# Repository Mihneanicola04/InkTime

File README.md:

# InkTime - Smartwatch Open Source

**InkTime** este un start-up dedicat crearii unui smartwatch accesibil si open-source. Acest repository contine documentatia tehnica, fisierele de proiectare hardware (schematica si layout PCB), fisierele de productie si modelele 3D necesare pentru fabricarea dispozitivului.

## 1. Diagrama Bloc
Diagrama de mai jos ilustreaza arhitectura sistemului, evidentiind interconexiunile dintre microcontrolerul nRF52840 si modulele periferice (Display, IMU, Alimentare).

---

## 2. Bill of Materials (BOM)
Toate componentele au fost selectate pentru a fi compatibile cu asamblarea automata prin JLC PCB.

| Componenta / Modul | Descriere | Link Achizitie (JLC Parts) | Datasheet |
| :--- | :--- | :--- | :--- |
| **nRF52840** | SoC Bluetooth Low Energy | [Link JLC](https://jlcpcb.com/parts) | (https://infocenter.nordicsemi.com/) |
| **Display E-Paper** | Ecran cu consum redus | [Link JLC](https://jlcpcb.com/parts) |(https://jlcpcb.com/parts) |
| **Baterie Li-Po** | 3.7V, conectare directa pe pad-uri | [Link JLC](https://jlcpcb.com/parts) |(https://jlcpcb.com/parts) |
| **Senzor IMU** | Senzor de miscare (Accel/Gyro) | [Link JLC](https://jlcpcb.com/parts) | (https://jlcpcb.com/parts) |
| **Butoane SMD** | Tip 0201/0402 conform cerintelor | [Link JLC](https://jlcpcb.com/parts) |(https://jlcpcb.com/parts) |
| **Condensatoare** | 100nF (0201) / >100nF (0402) | [Link JLC](https://jlcpcb.com/parts) |(https://jlcpcb.com/parts) |

---

## 3. Functionalitate Hardware si Design

### Detalii Tehnice
* **Unitate de procesare:** nRF52840, ales pentru integrarea BLE si eficienta energetica.
* **Interfete de comunicatie:**
    * **SPI:** Utilizat pentru controlul ecranului e-paper pentru rate de refresh optime.
    * **I2C:** Utilizat pentru senzorul IMU si managementul bateriei.
* **Managementul energiei:** PCB-ul include circuite de protectie pentru bateria Li-Po. Consumul a fost optimizat prin utilizarea condensatoarelor de decuplare de 100nF amplasate imediat langa pinii de alimentare. Autonomia a fost calculata avand in vedere starea de sleep si timpii activi ai procesorului si display-ului.
* **PCB Design:** * Grosime PCB: **1mm**.
    * Trasee de putere (VCC, 3V3): **0.3mm**.
    * Trasee de date: **0.15mm**.
    * Plan de masa: Prezent pe ambele straturi (Top/Bottom) cu **Via Stitching** pentru integritatea semnalului radio.

### Mapare Pini nRF52840
| Pin nRF52840 | Componenta | Functie / Justificare |
| :--- | :--- | :--- |
| **P0.xx** | SPI CLK | Clock pentru ecranul e-paper |
| **P0.yy** | I2C SDA | Date pentru senzorul IMU |
| **P0.zz** | Buton 1 | Intrare digitala cu pull-up intern |
| **VBUS** | USB-C | Detectare alimentare si incarcare baterie |

---

## 4. Implementare si Decizii de Proiectare (Design Log)

In cadrul procesului de dezvoltare (EVT/DVT), s-au luat urmatoarele decizii tehnice:
1.  **Amplasare Componente:** Toate componentele au fost plasate pe layer-ul **TOP** pentru a simplifica procesul de fabricatie.
2.  **Antena:** A fost plasata la extremitatea placii, cu planul de masa decupat dedesubt pentru a evita atenuarea semnalului BLE.
3.  **Conectivitate Baterie:** Din ratiuni de spatiu in carcasa, s-a renuntat la conectorul JST, bateria fiind lipita direct pe test pad-urile dedicate.
4.  **Erori Acceptate:** Eroarea DRC "Only INPUT pins on NET ID" a fost ignorata conform specificatiilor, fiind un artefact al bibliotecii de simboluri.
5.  **Mecanica:** Carcasa a fost ajustata in Fusion360 pentru a asigura alinierea perfecta a portului USB-C si a butoanelor fizice.
---

## 5. Structura Repository
* `/Hardware`: Fisiere native Fusion360 (.sch, .brd).
* `/Manufacturing`: Fisiere Gerber, BOM si Pick and Place.
* `/Mechanical`: Modele 3D (STEP/Exploded view) si asamblarea in Fusion360.
* `/Images`: Randari ale produsului finit si ale PCB-ului.
---

## 6   . Licenta
Acest proiect este licentiat sub [Apache License 2.0](LICENSE).

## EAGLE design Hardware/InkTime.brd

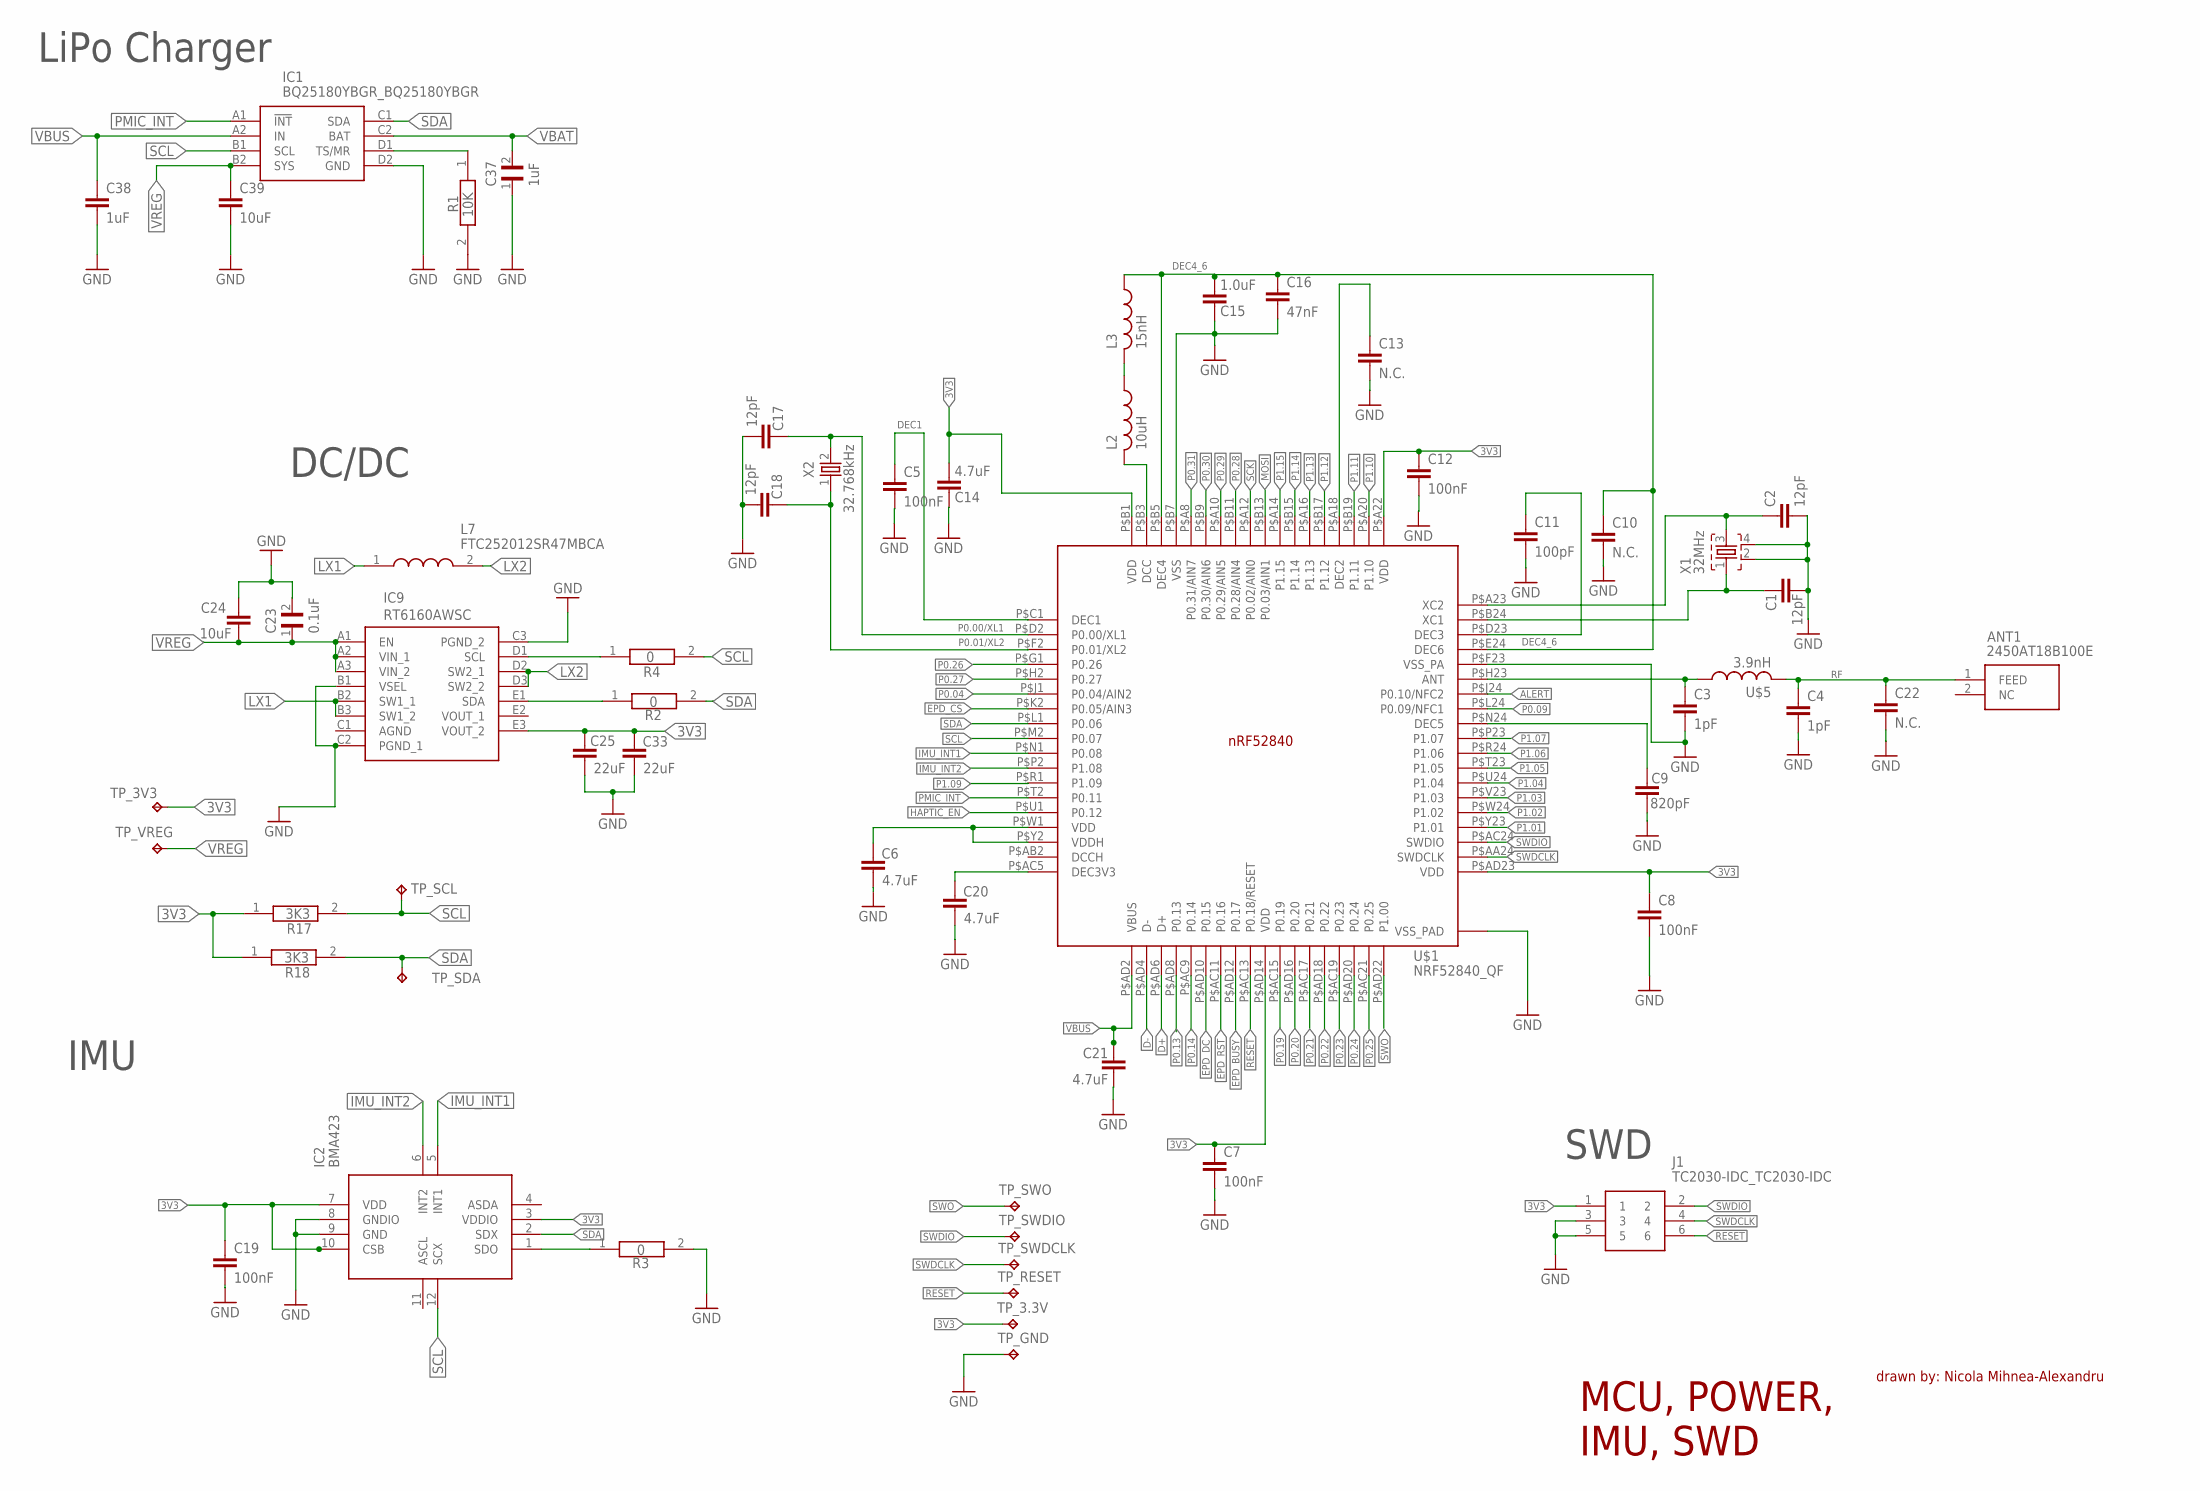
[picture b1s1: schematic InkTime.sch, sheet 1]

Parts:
ANT1: 2450AT18B100E; 2450AT18B100E_ANTC3216X140N
C1, C2, C17, C18: 12pF; NORDIC_NRF_3_RESC0201_N
C3, C4: 1pF; NORDIC_NRF_3_RESC0201_N
C5, C7, C8, C12, C19: 100nF; NORDIC_NRF_3_RESC0201_N
C6, C14, C20, C21: 4.7uF; NORDIC_NRF_3_RESC0402_N
C9: 820pF; NORDIC_NRF_3_RESC0201_N
C10, C13, C22: N.C.; NORDIC_NRF_3_RESC0201_N
C11: 100pF; NORDIC_NRF_3_RESC0201_N
C15: 1.0uF; NORDIC_NRF_3_RESC0402_N
C16: 47nF; NORDIC_NRF_3_RESC0201_N
C23: 0.1uF; GRM011R60J152KE01L_2_CAPC0201X13N
C24, C39: 10uF; NORDIC_NRF_3_RESC0402_N
C25, C33: 22uF; NORDIC_NRF_3_RESC0402_N
C37: 1uF; GRM011R60J152KE01L_2_CAPC0201X13N
C38: 1uF; NORDIC_NRF_3_RESC0402_N
IC1: BQ25180YBGR_BQ25180YBGR; BQ25180YBGR_BGA8C40P2X4_100X155X50
IC2: BMA423; BMA423_BMA423
IC9: RT6160AWSC; RT6160AWSC_BGA15C40P3X5_140X230X60
J1: TC2030-IDC_TC2030-IDC; TC2030-IDC_TC2030IDC
L2: 10uH; NORDIC_NRF_2_RESC0201_N
L3: 15nH; NORDIC_NRF_2_RESC0201_N
L7: FTC252012SR47MBCA; MLP2016SR47MT0S1_INDC2016X100N
R1: 10K; CPF0201D7K68C1_0201
R2, R3, R4: 0; CPF0201D7K68C1_0201
R17, R18: 3K3; CPF0201D7K68C1_0201
TP_3.3V, TP_3V3: HECTOR_WATCH_1_TPTP20R; HECTOR_WATCH_1_TP20R
TP_GND: HECTOR_WATCH_1_TPTP20R; HECTOR_WATCH_1_TP20R
TP_RESET: HECTOR_WATCH_1_TPTP20R; HECTOR_WATCH_1_TP20R
TP_SCL: HECTOR_WATCH_1_TPTP20R; HECTOR_WATCH_1_TP20R
TP_SDA: HECTOR_WATCH_1_TPTP20R; HECTOR_WATCH_1_TP20R
TP_SWDCLK: HECTOR_WATCH_1_TPTP20R; HECTOR_WATCH_1_TP20R
TP_SWDIO: HECTOR_WATCH_1_TPTP20R; HECTOR_WATCH_1_TP20R
TP_SWO: HECTOR_WATCH_1_TPTP20R; HECTOR_WATCH_1_TP20R
TP_VREG: HECTOR_WATCH_1_TPTP20R; HECTOR_WATCH_1_TP20R
U$1: NRF52840_QF; NORDIC_NRF_4_AQFN50P700X700X85_HS-74N
U$5: 3.9nH; NORDIC_NRF_2_RESC0201_N
X1: 32MHz; NORDIC_NRF_BT-XTAL_2016_N
X2: 32.768kHz; NORDIC_NRF_1_XTAL_3215_N

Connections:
3V3: C7.1, C8.1, C12.1, C14.2, C19.1, C25.1, C33.1, IC2.3 (VDDIO), IC9.E3 (VOUT_2), J1.1, R17.1, R18.1, TP_3.3V.TP, TP_3V3.TP, U$1.P$A22 (VDD), U$1.P$AD14 (VDD), U$1.P$AD23 (VDD), U$1.P$B1 (VDD); also elsewhere on the board
ALERT: U$1.P$J24 (P0.10/NFC2); also elsewhere on the board
D+: U$1.P$AD6 (D+); also elsewhere on the board
D-: U$1.P$AD4 (D-); also elsewhere on the board
DEC1: C5.1, U$1.P$C1 (DEC1)
DEC4_6: C10.1, C15.2, C16.1, L3.1, U$1.P$B5 (DEC4), U$1.P$E24 (DEC6)
EPD_BUSY: U$1.P$AD12 (P0.17); also elsewhere on the board
EPD_CS: U$1.P$K2 (P0.05/AIN3); also elsewhere on the board
EPD_DC: U$1.P$AD10 (P0.15); also elsewhere on the board
EPD_RST: U$1.P$AC11 (P0.16); also elsewhere on the board
GND: C1.2, C2.2, C3.2, C4.2, C5.2, C6.2, C7.2, C8.2, C9.2, C10.2, C11.2, C12.2, C13.2, C14.1, C15.1, C16.2, C17.2, C18.2, C19.2, C20.2, C21.2, C22.2, C23.2, C24.1, C25.2, C33.2, C37.1, C38.2, C39.2, IC1.D2 (GND), IC2.8 (GNDIO), IC2.9 (GND), IC9.B1 (VSEL), IC9.C2 (PGND_1), IC9.C3 (PGND_2), J1.3, J1.5, R1.2, R3.2, TP_GND.TP, U$1.P$74 (VSS_PAD), U$1.P$75 (VSS_PAD), U$1.P$76 (VSS_PAD), U$1.P$77 (VSS_PAD), U$1.P$78 (VSS_PAD), U$1.P$79 (VSS_PAD), U$1.P$80 (VSS_PAD), U$1.P$81 (VSS_PAD), U$1.P$82 (VSS_PAD), U$1.P$83 (VSS_PAD), U$1.P$84 (VSS_PAD), U$1.P$85 (VSS_PAD), U$1.P$86 (VSS_PAD), U$1.P$87 (VSS_PAD), U$1.P$88 (VSS_PAD), U$1.P$89 (VSS_PAD), U$1.P$90 (VSS_PAD), U$1.P$B7 (VSS), U$1.P$F23 (VSS_PA), X1.2, X1.4; also elsewhere on the board
HAPTIC_EN: U$1.P$U1 (P0.12); also elsewhere on the board
IMU_INT1: IC2.5 (INT1), U$1.P$N1 (P0.08)
IMU_INT2: IC2.6 (INT2), U$1.P$P2 (P1.08)
LX1: IC9.B2 (SW1_1), IC9.B3 (SW1_2), L7.1
LX2: IC9.D2 (SW2_1), IC9.D3 (SW2_2), L7.2
MOSI: U$1.P$B13 (P0.03/AIN1); also elsewhere on the board
unnamed: C20.1, U$1.P$AC5 (DEC3V3)
unnamed: IC9.D1 (SCL), R4.1
unnamed: IC9.E1 (SDA), R2.1
unnamed: IC1.D1 (TS/MR), R1.1
unnamed: C6.1, U$1.P$W1 (VDD)
unnamed: IC2.7 (VDD), IC2.10 (CSB)
unnamed: L2.2, U$1.P$B3 (DCC)
unnamed: L2.1, L3.2
unnamed: IC2.1 (SDO), R3.1
unnamed: C11.1, U$1.P$D23 (DEC3)
unnamed: C2.1, U$1.P$A23 (XC2), X1.3
unnamed: C13.1, U$1.P$A18 (DEC2)
unnamed: C1.1, U$1.P$B24 (XC1), X1.1
unnamed: C3.1, U$1.P$H23 (ANT), U$5.1
unnamed: C9.1, U$1.P$N24 (DEC5)
P0.00/XL1: C17.1, U$1.P$D2 (P0.00/XL1), X2.2
P0.01/XL2: C18.1, U$1.P$F2 (P0.01/XL2), X2.1
P0.04: U$1.P$J1 (P0.04/AIN2)
P0.09: U$1.P$L24 (P0.09/NFC1)
P0.13: U$1.P$AD8 (P0.13); also elsewhere on the board
P0.14: U$1.P$AC9 (P0.14); also elsewhere on the board
P0.19: U$1.P$AC15 (P0.19)
P0.20: U$1.P$AD16 (P0.20)
P0.21: U$1.P$AC17 (P0.21)
P0.22: U$1.P$AD18 (P0.22)
P0.23: U$1.P$AC19 (P0.23)
P0.24: U$1.P$AD20 (P0.24)
P0.25: U$1.P$AC21 (P0.25)
P0.26: U$1.P$G1 (P0.26)
P0.27: U$1.P$H2 (P0.27)
P0.28: U$1.P$B11 (P0.28/AIN4)
P0.29: U$1.P$A10 (P0.29/AIN5)
P0.30: U$1.P$B9 (P0.30/AIN6)
P0.31: U$1.P$A8 (P0.31/AIN7)
P1.01: U$1.P$Y23 (P1.01); also elsewhere on the board
P1.02: U$1.P$W24 (P1.02); also elsewhere on the board
P1.03: U$1.P$V23 (P1.03)
P1.04: U$1.P$U24 (P1.04)
P1.05: U$1.P$T23 (P1.05)
P1.06: U$1.P$R24 (P1.06)
P1.07: U$1.P$P23 (P1.07)
P1.09: U$1.P$R1 (P1.09)
P1.10: U$1.P$A20 (P1.10)
P1.11: U$1.P$B19 (P1.11)
P1.12: U$1.P$B17 (P1.12)
P1.13: U$1.P$A16 (P1.13)
P1.14: U$1.P$B15 (P1.14)
P1.15: U$1.P$A14 (P1.15)
PMIC_INT: IC1.A1 (!INT), U$1.P$T2 (P0.11)
RESET: J1.6, TP_RESET.TP, U$1.P$AC13 (P0.18/RESET)
RF: ANT1.1 (FEED), C4.1, C22.1, U$5.2
SCK: U$1.P$A12 (P0.02/AIN0); also elsewhere on the board
SCL: IC1.B1 (SCL), IC2.12 (SCX), R4.2, R17.2, TP_SCL.TP, U$1.P$M2 (P0.07); also elsewhere on the board
SDA: IC1.C1 (SDA), IC2.2 (SDX), R2.2, R18.2, TP_SDA.TP, U$1.P$L1 (P0.06); also elsewhere on the board
SWDCLK: J1.4, TP_SWDCLK.TP, U$1.P$AA24 (SWDCLK)
SWDIO: J1.2, TP_SWDIO.TP, U$1.P$AC24 (SWDIO)
SWO: TP_SWO.TP, U$1.P$AD22 (P1.00)
VBAT: C37.2, IC1.C2 (BAT); also elsewhere on the board
VBUS: C21.1, C38.1, IC1.A2 (IN), U$1.P$AD2 (VBUS); also elsewhere on the board
VREG: C23.1, C24.2, C39.1, IC1.B2 (SYS), IC9.A1 (EN), IC9.A2 (VIN_1), IC9.A3 (VIN_2), TP_VREG.TP

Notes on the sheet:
LiPo Charger
DC/DC
IMU
SWD
MCU, POWER, IMU, SWD
drawn by: Nicola Mihnea-Alexandru

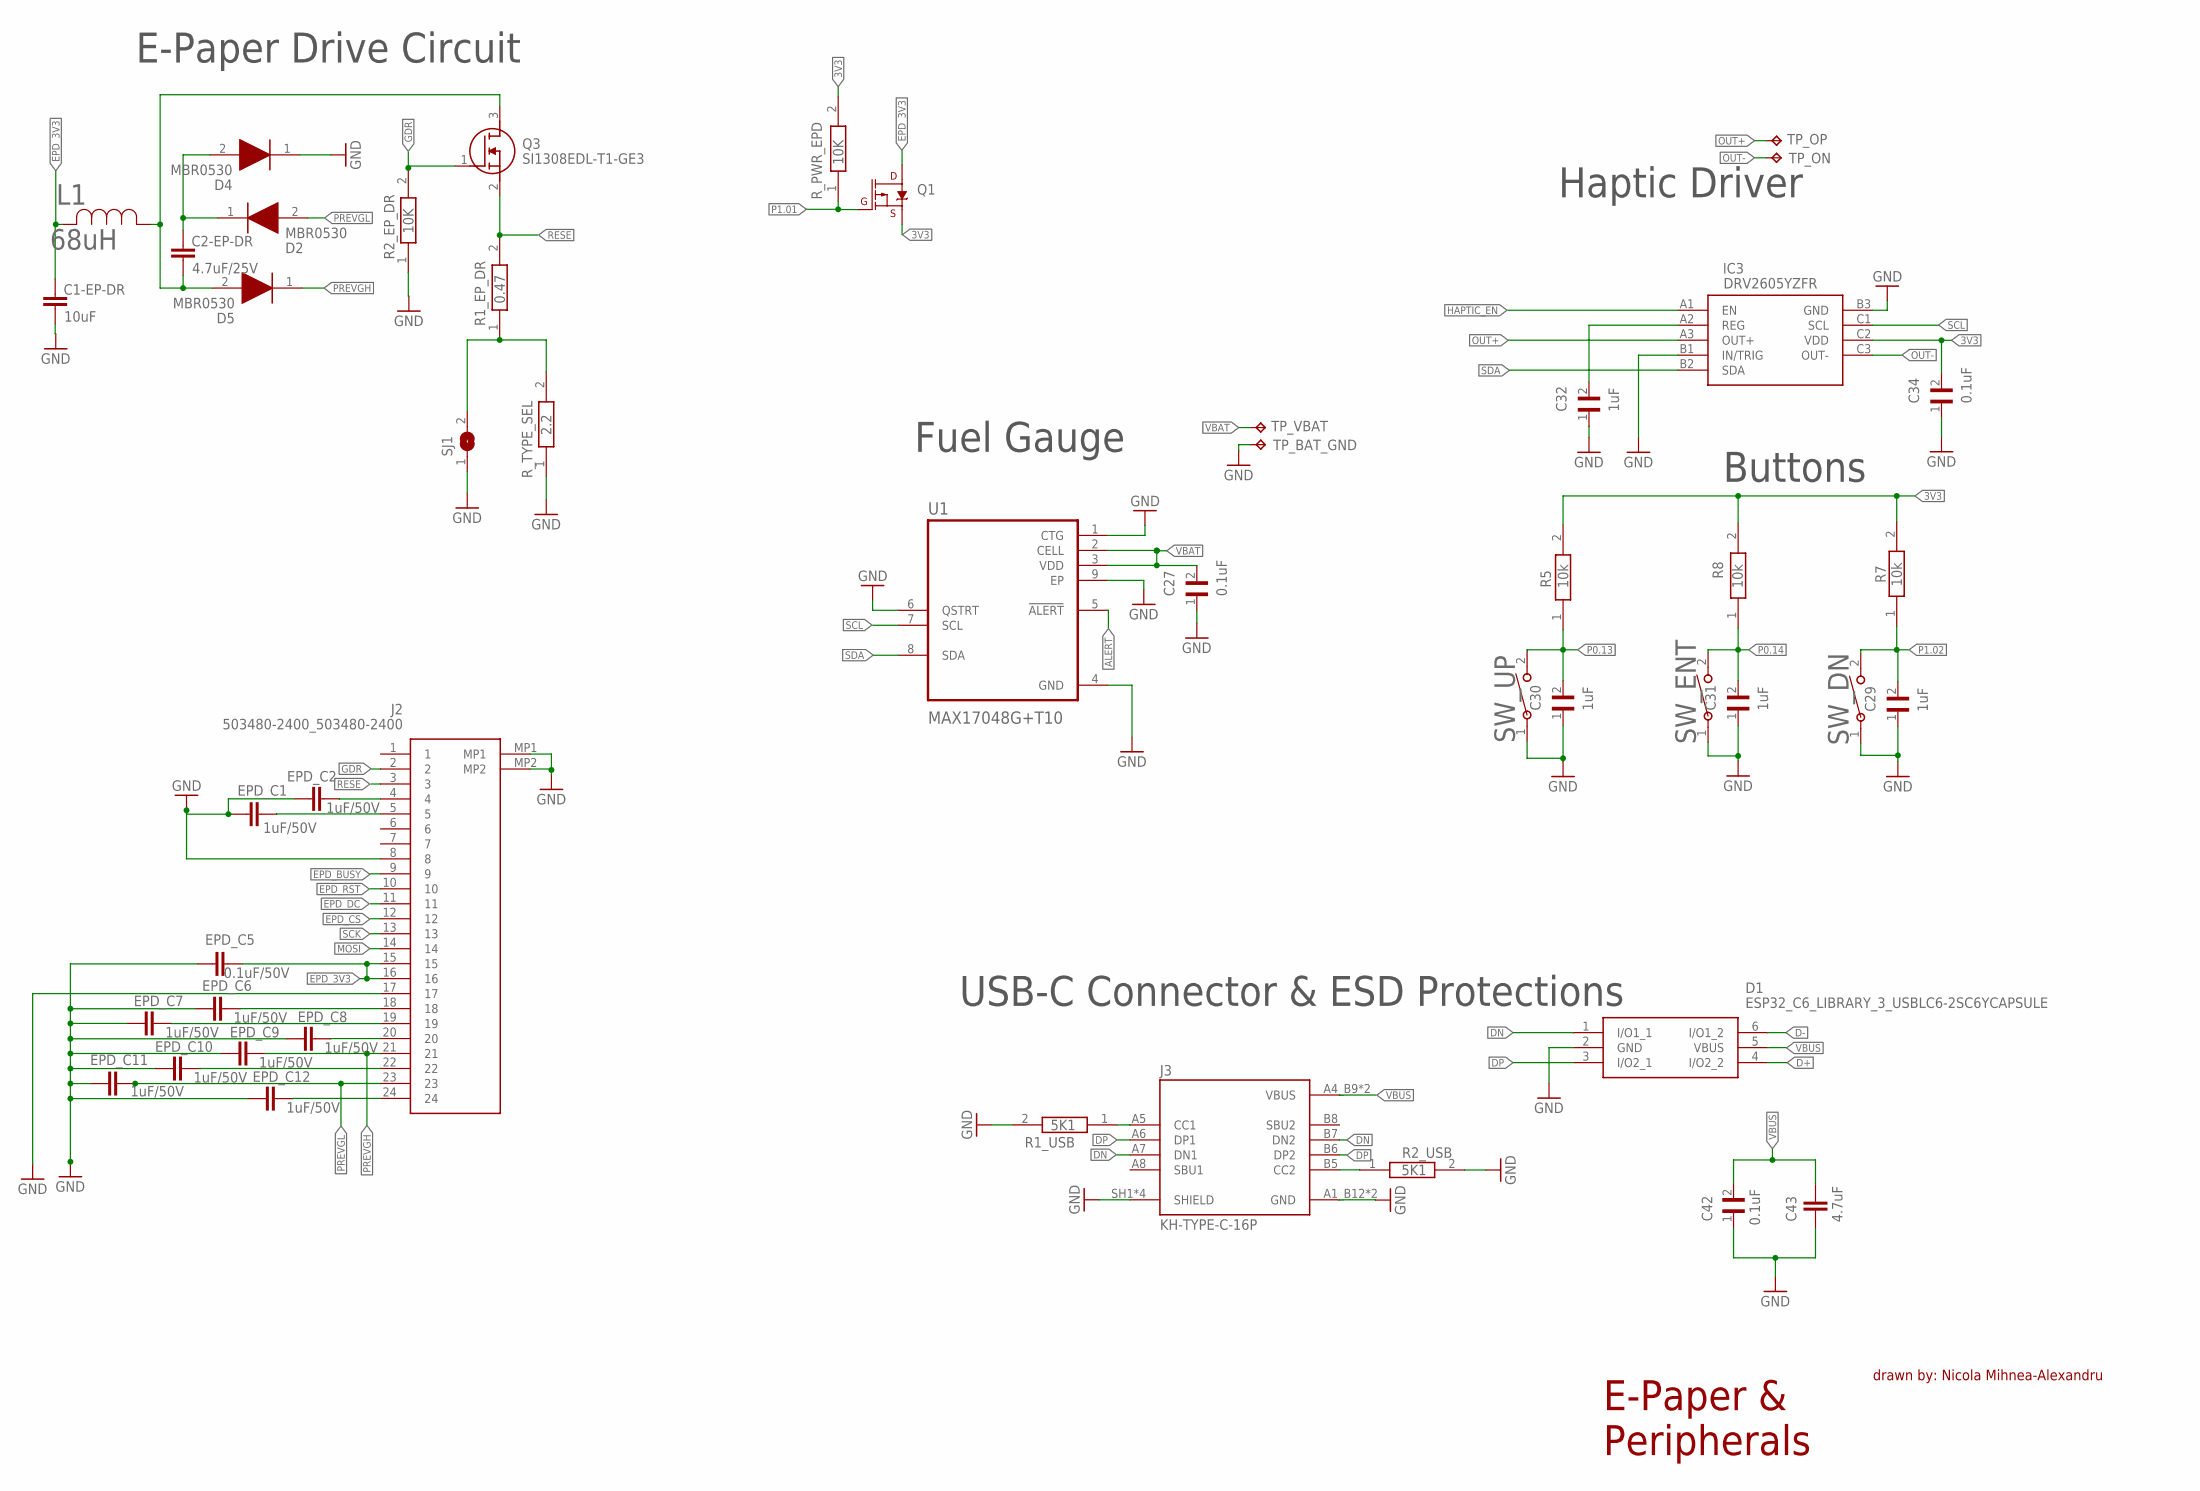
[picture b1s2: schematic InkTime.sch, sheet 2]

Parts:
C1-EP-DR: 10uF; NORDIC_NRF_3_RESC0402_N
C2-EP-DR: 4.7uF/25V; NORDIC_NRF_3_RESC0402_N
C27, C34, C42: 0.1uF; GRM011R60J152KE01L_2_CAPC0201X13N
C29, C30, C31, C32: 1uF; GRM011R60J152KE01L_2_CAPC0201X13N
C43: 4.7uF; NORDIC_NRF_3_RESC0402_N
D1: ESP32_C6_LIBRARY_3_USBLC6-2SC6YCAPSULE; ESP32_C6_LIBRARY_3_SOT95P280X145-6N
D2, D4, D5: MBR0530; ESP32_C6_LIBRARY_5_SOD3716X135N
EPD_C1, EPD_C2, EPD_C6, EPD_C7, EPD_C8, EPD_C9, EPD_C10, EPD_C11, EPD_C12: 1uF/50V; NORDIC_NRF_3_RESC0402_N
EPD_C5: 0.1uF/50V; NORDIC_NRF_3_RESC0402_N
IC3: DRV2605YZFR; DRV2605YZFR_BGA9C50P3X3_144X144X62
J2: 503480-2400_503480-2400; 503480-2400_5034802400
J3: KH-TYPE-C-16P; KH-TYPE-C-16P_KINGHELM_KH-TYPE-C-16P
L1: 68uH; ESP32_C6_LIBRARY_2_IND_4828-WE-TPC_WRE
Q1: ESP32_C6_LIBRARY_4_ESP32_WROVER_SPARKFUN-DISCRETE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; ESP32_C6_LIBRARY_4_ESP32_C6_LIBRARY_4_ESP32_C6_LIBRARY_4_ES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
Q3: SI1308EDL-T1-GE3; ESP32_C6_LIBRARY_6_SOT65P210X110-3N
R1_EP_DR: 0.47; CPF0201D7K68C1_0201
R1_USB, R2_USB: 5K1; CPF0201D7K68C1_0201
R2_EP_DR: 10K; CPF0201D7K68C1_0201
R5, R7, R8: 10k; CPF0201D7K68C1_0201
R_PWR_EPD: 10K; CPF0201D7K68C1_0201
R_TYPE_SEL: 2.2; CPF0201D7K68C1_0201
SJ1: ESP32_C6_LIBRARY_7_JUMPER_SJ
SW_DN: 2025-10-22_07-23-44_LIBRARY_EVP-AKE31A; 2025-10-22_07-23-44_LIBRARY_SW_EVP-AKE31A_PAN
SW_ENT: 2025-10-22_07-23-44_LIBRARY_EVP-AKE31A; 2025-10-22_07-23-44_LIBRARY_SW_EVP-AKE31A_PAN
SW_UP: 2025-10-22_07-23-44_LIBRARY_EVP-AKE31A; 2025-10-22_07-23-44_LIBRARY_SW_EVP-AKE31A_PAN
TP_BAT_GND: HECTOR_WATCH_1_TPTP20R; HECTOR_WATCH_1_TP20R
TP_ON: HECTOR_WATCH_1_TPTP20R; HECTOR_WATCH_1_TP20R
TP_OP: HECTOR_WATCH_1_TPTP20R; HECTOR_WATCH_1_TP20R
TP_VBAT: HECTOR_WATCH_1_TPTP20R; HECTOR_WATCH_1_TP20R
U1: MAX17048G+T10; ESP32_C6_LIBRARY_SON50P200X200X80-9N

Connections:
3V3: C34.2, IC3.C2 (VDD), Q1.2 (S), R5.2, R7.2, R8.2, R_PWR_EPD.2; also elsewhere on the board
ALERT: U1.5 (!ALERT); also elsewhere on the board
D+: D1.4 (I/O2_2); also elsewhere on the board
D-: D1.6 (I/O1_2); also elsewhere on the board
DN: D1.1 (I/O1_1), J3.A7 (DN1), J3.B7 (DN2)
DP: D1.3 (I/O2_1), J3.A6 (DP1), J3.B6 (DP2)
EPD_3V3: C1-EP-DR.1, EPD_C5.2, J2.15, J2.16, L1.2, Q1.3 (D)
EPD_BUSY: J2.9; also elsewhere on the board
EPD_CS: J2.12; also elsewhere on the board
EPD_DC: J2.11; also elsewhere on the board
EPD_RST: J2.10; also elsewhere on the board
GDR: J2.2, Q3.1 (G), R2_EP_DR.2
GND: C1-EP-DR.2, C27.1, C29.1, C30.1, C31.1, C32.1, C34.1, C42.1, C43.1, D1.2 (GND), D4.1 (K), EPD_C1.1, EPD_C2.1, EPD_C5.1, EPD_C6.1, EPD_C7.1, EPD_C8.1, EPD_C9.1, EPD_C10.1, EPD_C11.1, EPD_C12.1, IC3.B1 (IN/TRIG), IC3.B3 (GND), J2.8, J2.17, J2.MP1, J2.MP2, J3.A1_B12 (GND), J3.A12_B1 (GND), J3.SH1 (SHIELD), J3.SH2 (SHIELD), J3.SH3 (SHIELD), J3.SH4 (SHIELD), R1_USB.2, R2_EP_DR.1, R2_USB.2, R_TYPE_SEL.1, SJ1.1, SW_DN.1, SW_ENT.1, SW_UP.1, TP_BAT_GND.TP, U1.1 (CTG), U1.4 (GND), U1.6 (QSTRT), U1.9 (EP); also elsewhere on the board
HAPTIC_EN: IC3.A1 (EN); also elsewhere on the board
MOSI: J2.14; also elsewhere on the board
unnamed: C32.2, IC3.A2 (REG)
unnamed: C2-EP-DR.2, D5.2 (A), L1.1, Q3.3 (D)
unnamed: C2-EP-DR.1, D2.1 (K), D4.2 (A)
unnamed: EPD_C2.2, J2.4
unnamed: EPD_C1.2, J2.5
unnamed: R1_EP_DR.1, R_TYPE_SEL.2, SJ1.2
unnamed: J3.A5 (CC1), R1_USB.1
unnamed: J3.B5 (CC2), R2_USB.1
unnamed: EPD_C10.2, J2.22
unnamed: EPD_C6.2, J2.18
unnamed: EPD_C7.2, J2.19
unnamed: EPD_C8.2, J2.20
unnamed: EPD_C12.2, J2.24
OUT+: IC3.A3 (OUT+), TP_OP.TP
OUT-: IC3.C3 (OUT-), TP_ON.TP
P0.13: C30.2, R5.1, SW_UP.2; also elsewhere on the board
P0.14: C31.2, R8.1, SW_ENT.2; also elsewhere on the board
P1.01: Q1.1 (G), R_PWR_EPD.1; also elsewhere on the board
P1.02: C29.2, R7.1, SW_DN.2; also elsewhere on the board
PREVGH: D5.1 (K), EPD_C9.2, J2.21
PREVGL: D2.2 (A), EPD_C11.2, J2.23
RESE: J2.3, Q3.2 (S), R1_EP_DR.2
SCK: J2.13; also elsewhere on the board
SCL: IC3.C1 (SCL), U1.7 (SCL); also elsewhere on the board
SDA: IC3.B2 (SDA), U1.8 (SDA); also elsewhere on the board
VBAT: C27.2, TP_VBAT.TP, U1.2 (CELL), U1.3 (VDD); also elsewhere on the board
VBUS: C42.2, C43.2, D1.5 (VBUS), J3.A4_B9 (VBUS), J3.A9_B4 (VBUS); also elsewhere on the board

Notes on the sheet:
E-Paper Drive Circuit
Fuel Gauge
Haptic Driver
Buttons
USB-C Connector & ESD Protections
E-Paper & Peripherals
drawn by: Nicola Mihnea-Alexandru

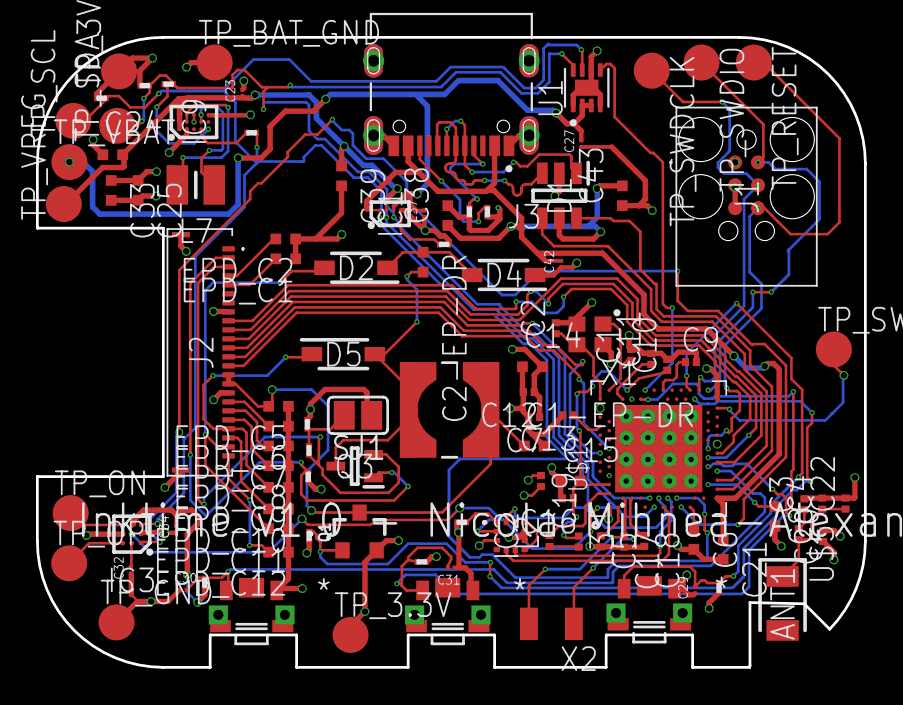
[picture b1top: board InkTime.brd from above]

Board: 4 copper layers, 46.0 x 35.0 mm, 105 parts (0 on the bottom side), 72 nets.

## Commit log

2026-04-10 Initial plan
2026-04-10 Create project folder structure: Hardware, Manufacturing, Mechanical, Images
    Agent-Logs-Url: https://github.com/Mihneanicola04/InkTime/sessions/4e57e2ca-3f50-4929-856a-f12f4a0e7cc2
2026-04-10 Added schematic
2026-04-10 Added BOM
2026-04-10 Added readme
2026-04-21 Added manufacturing
2026-04-21 Added sch after dvt
2026-04-21 Added files after DVT review
2026-04-21 Added diagram
2026-04-21 Updated readme
    Removed rendering section and updated license section.

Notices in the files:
parts and their libraries:
COPYRIGHT: Copyright (C) 2024 Ultra Librarian. All rights reserved.
InkTime_v5: COPYRIGHT: Copyright (C) 2025 Ultra Librarian. All rights reserved.
